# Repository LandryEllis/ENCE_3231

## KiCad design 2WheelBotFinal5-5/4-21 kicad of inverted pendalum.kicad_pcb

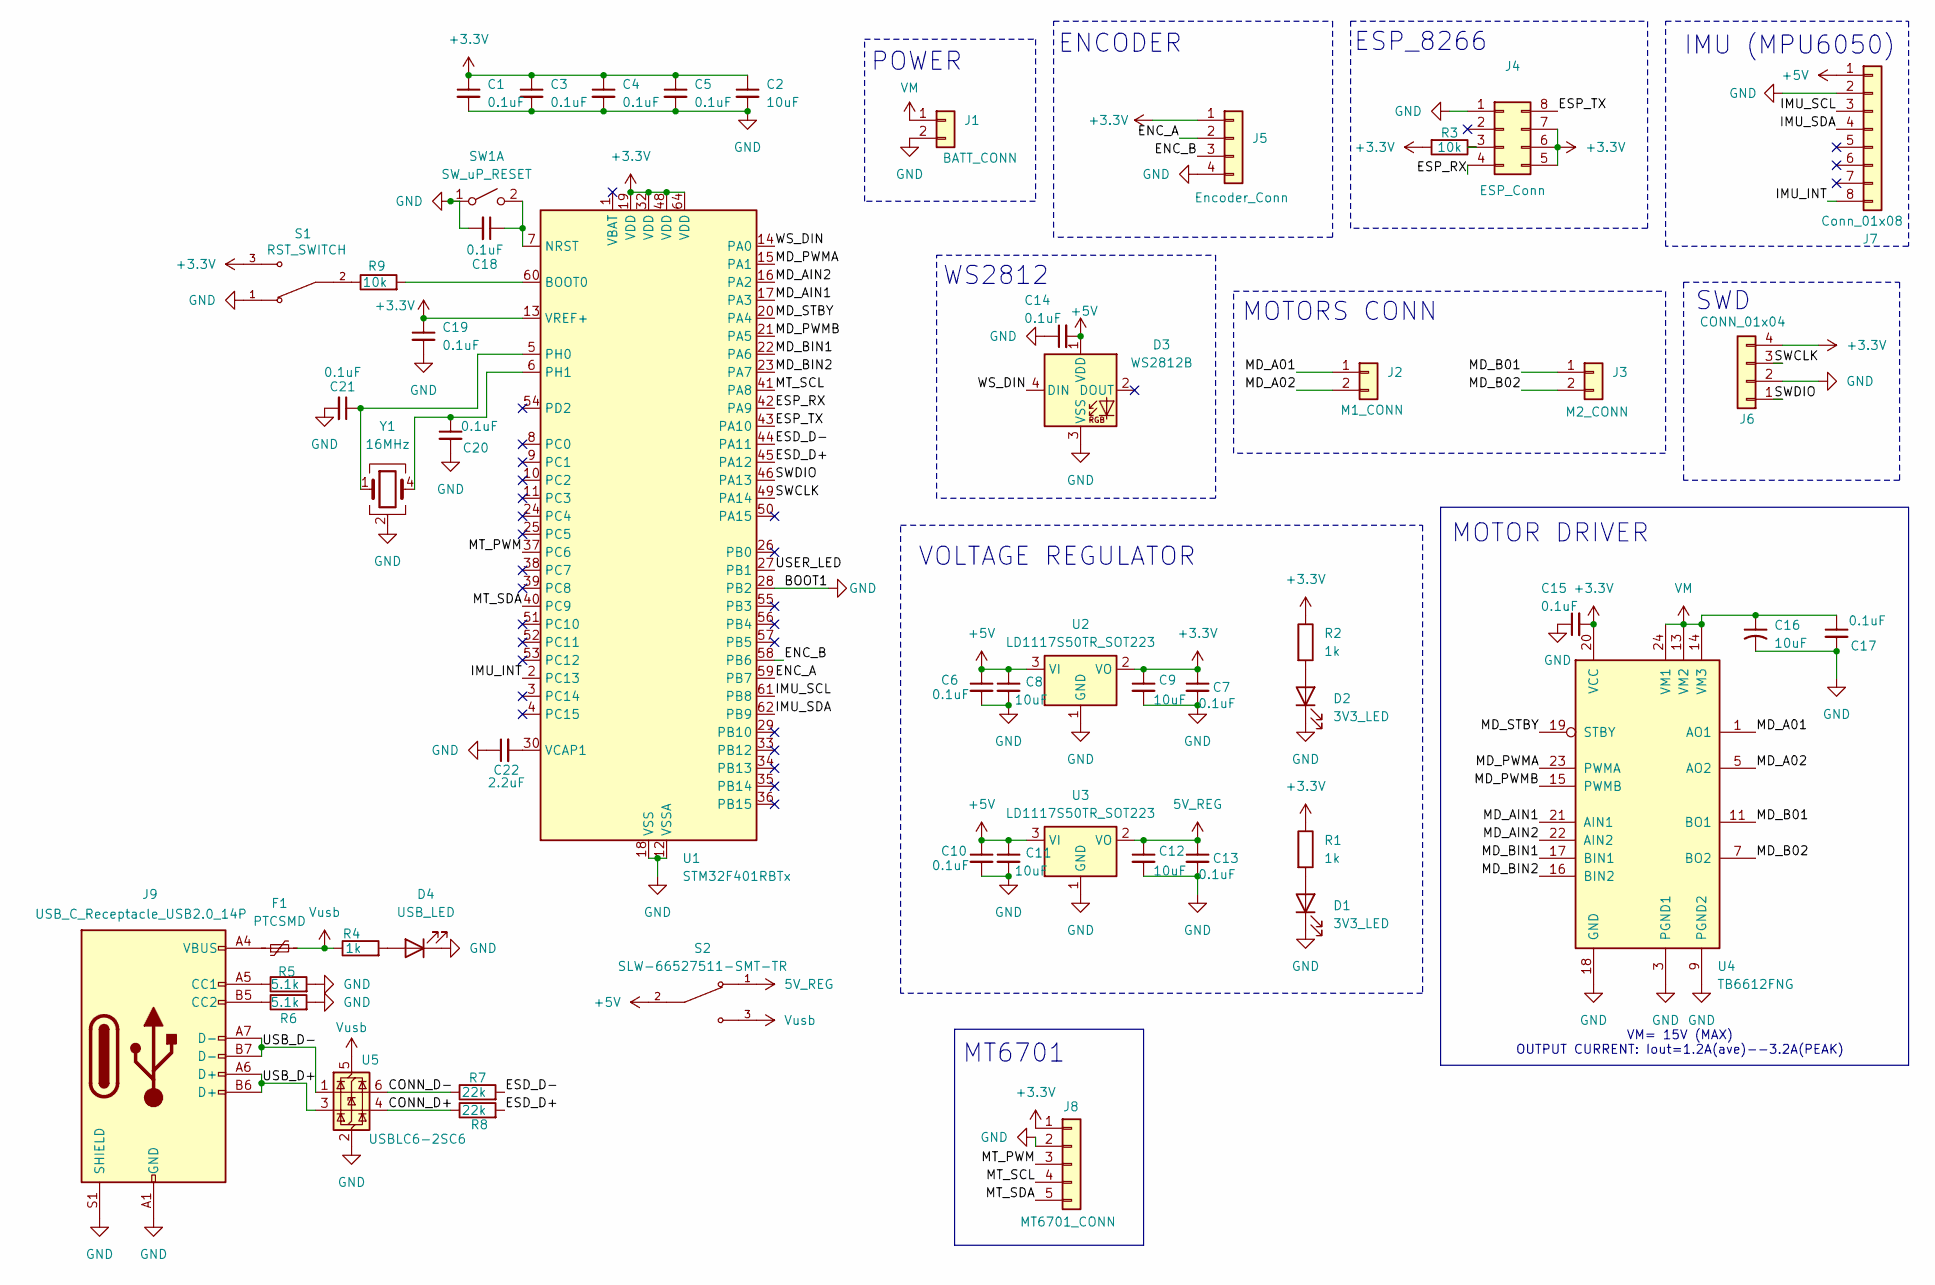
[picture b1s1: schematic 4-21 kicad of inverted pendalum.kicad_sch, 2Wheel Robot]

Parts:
C1, C3, C4, C5, C6, C7, C10, C13, C14, C15, C17, C18, C19, C20, C21: 0.1uF; C_0805_2012Metric_Pad1.18x1.45mm_HandSolder; mfr. # KYOCERA AVX
C2, C8, C9, C11, C12: 10uF; C_0805_2012Metric_Pad1.18x1.45mm_HandSolder; Mouser # 963-MCASL21GBB7106KT
C16: 10uF; C_0805_2012Metric_Pad1.18x1.45mm_HandSolder
C22: 2.2uF; C_0805_2012Metric_Pad1.18x1.45mm_HandSolder
D1, D2: 3V3_LED; LED_0805_2012Metric_Pad1.15x1.40mm_HandSolder
D3: WS2812B; LED_WS2812B_PLCC4_5.0x5.0mm_P3.2mm
D4: USB_LED; LED_0805_2012Metric_Pad1.15x1.40mm_HandSolder
F1: PTCSMD; Fuse_1812_4532Metric
J1: BATT_CONN; JST_XH_B2B-XH-A_1x02_P2.50mm_Vertical
J2: M1_CONN; JST_XH_B2B-XH-A_1x02_P2.50mm_Vertical
J3: M2_CONN; JST_XH_B2B-XH-A_1x02_P2.50mm_Vertical
J4: ESP_Conn; PinSocket_2x04_P2.54mm_Vertical
J5: Encoder_Conn; JST_XH_B4B-XH-A_1x04_P2.50mm_Vertical
J6: CONN_01x04; PinHeader_1x04_P2.54mm_Vertical
J7: Conn_01x08; PinSocket_1x08_P2.54mm_Vertical
J8: MT6701_CONN; JST_XH_B5B-XH-A_1x05_P2.50mm_Vertical
J9: USB_C_Receptacle_USB2.0_14P; USB_C_Receptacle_HCTL_HC-TYPE-C-16P-01A
R1, R2, R4: 1k; R_0805_2012Metric_Pad1.20x1.40mm_HandSolder
R3, R9: 10k; R_0805_2012Metric_Pad1.20x1.40mm_HandSolder
R5, R6: 5.1k; R_0805_2012Metric_Pad1.20x1.40mm_HandSolder
R7, R8: 22k; R_0805_2012Metric_Pad1.20x1.40mm_HandSolder
S1: RST_SWITCH; SW_SLW-66527511-SMT-TR; PARTREV 1.01
S2: SLW-66527511-SMT-TR; SW_SLW-66527511-SMT-TR; PARTREV 1.01
SW1: SW_uP_RESET; SW_uP_Reset
U1: STM32F401RBTx; LQFP-64_10x10mm_P0.5mm; Mfr. # STM32F401RET6
U2, U3: LD1117S50TR_SOT223; SOT-223-3_TabPin2; Mouser # 511-LD1117S50
U4: TB6612FNG; SSOP-24_5.3x8.2mm_P0.65mm
U5: USBLC6-2SC6; SOT-23-6
Y1: 16MHz; Crystal_SMD_Abracon_ABM8G-4Pin_3.2x2.5mm

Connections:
5V_REG: C12.1, C13.1, S2.1, U3.2 (VO)
+3.3V: C1.1, C2.1, C3.1, C4.1, C5.1, C7.1, C9.1, C15.2, C19.1, J4.5, J4.6, J4.7, J5.1, J6.4, J8.1, R1.1, R2.1, R3.2, S1.3, U1.13 (VREF+), U1.19 (VDD), U1.32 (VDD), U1.48 (VDD), U1.64 (VDD), U2.2 (VO), U4.20 (VCC)
+5V: C6.1, C8.1, C10.1, C11.1, C14.2, D3.1 (VDD), J7.1, S2.2, U2.3 (VI), U3.3 (VI)
/CONN_D+: R8.1, U5.4 (I/O2)
/CONN_D-: R7.1, U5.6 (I/O1)
/ENC_A: J5.2, U1.59 (PB7)
/ENC_B: J5.3, U1.58 (PB6)
/ESD_D+: R8.2, U1.45 (PA12)
/ESD_D-: R7.2, U1.44 (PA11)
/ESP_RX: J4.4, U1.42 (PA9)
/ESP_TX: J4.8, U1.43 (PA10)
/IMU_INT: J7.8, U1.2 (PC13)
/IMU_SCL: J7.3, U1.61 (PB8)
/IMU_SDA: J7.4, U1.62 (PB9)
/MD_A01: J2.1, U4.1 (AO1), U4.2 (AO1)
/MD_A02: J2.2, U4.5 (AO2), U4.6 (AO2)
/MD_AIN1: U1.17 (PA3), U4.21 (AIN1)
/MD_AIN2: U1.16 (PA2), U4.22 (AIN2)
/MD_B01: J3.1, U4.11 (BO1), U4.12 (BO1)
/MD_B02: J3.2, U4.7 (BO2), U4.8 (BO2)
/MD_BIN1: U1.22 (PA6), U4.17 (BIN1)
/MD_BIN2: U1.23 (PA7), U4.16 (BIN2)
/MD_PWMA: U1.15 (PA1), U4.23 (PWMA)
/MD_PWMB: U1.21 (PA5), U4.15 (PWMB)
/MD_STBY: U1.20 (PA4), U4.19 (STBY)
/MT_PWM: J8.3, U1.37 (PC6)
/MT_SCL: J8.4, U1.41 (PA8)
/MT_SDA: J8.5, U1.40 (PC9)
/SWCLK: J6.3, U1.49 (PA14)
/SWDIO: J6.1, U1.46 (PA13)
/USB_D+: J9.A6 (D+), J9.B6 (D+), U5.3 (I/O2)
/USB_D-: J9.A7 (D-), J9.B7 (D-), U5.1 (I/O1)
/USER_LED: U1.27 (PB1)
/WS_DIN: D3.4 (DIN), U1.14 (PA0)
GND: C1.2, C2.2, C3.2, C4.2, C5.2, C6.2, C7.2, C8.2, C9.2, C10.2, C11.2, C12.2, C13.2, C14.1, C15.1, C16.2, C17.2, C18.2, C19.2, C20.2, C21.2, C22.1, D1.1 (K), D2.1 (K), D3.3 (VSS), D4.1 (K), J1.2, J4.1, J5.4, J6.2, J7.2, J8.2, J9.A1 (GND), J9.A12 (GND), J9.B1 (GND), J9.B12 (GND), J9.S1 (SHIELD), R5.2, R6.2, S1.1, SW1.1 (A), U1.12 (VSSA), U1.18 (VSS), U1.28 (PB2), U1.31 (VSS), U1.47 (VSS), U1.63 (VSS), U2.1 (GND), U3.1 (GND), U4.3 (PGND1), U4.4 (PGND1), U4.9 (PGND2), U4.10 (PGND2), U4.18 (GND), U5.2 (GND), Y1.2 (G), Y1.3 (G)
unnamed: D1.2 (A), R1.2
unnamed: D2.2 (A), R2.2
unnamed: D4.2 (A), R4.2
unnamed: F1.1, J9.A4 (VBUS), J9.A9 (VBUS), J9.B4 (VBUS), J9.B9 (VBUS)
unnamed: J4.3, R3.1
unnamed: J9.A5 (CC1), R5.1
unnamed: J9.B5 (CC2), R6.1
unnamed: R9.1, S1.2
unnamed: C18.1, SW1.2 (B), U1.7 (NRST)
unnamed: R9.2, U1.60 (BOOT0)
unnamed: C21.1, U1.5 (PH0), Y1.1
unnamed: C20.1, U1.6 (PH1), Y1.4
unnamed: C22.2, U1.30 (VCAP1)
VM: C16.1, C17.1, J1.1, U4.13 (VM2), U4.14 (VM3), U4.24 (VM1)
Vusb: F1.2, R4.1, S2.3, U5.5 (VBUS)

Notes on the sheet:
VM= 15V (MAX) OUTPUT CURRENT: Iout=1.2A(ave)--3.2A(PEAK)
ESP_8266
IMU (MPU6050)
MT6701
SWD
MOTORS CONN
POWER
ENCODER
WS2812
VOLTAGE REGULATOR
MOTOR DRIVER

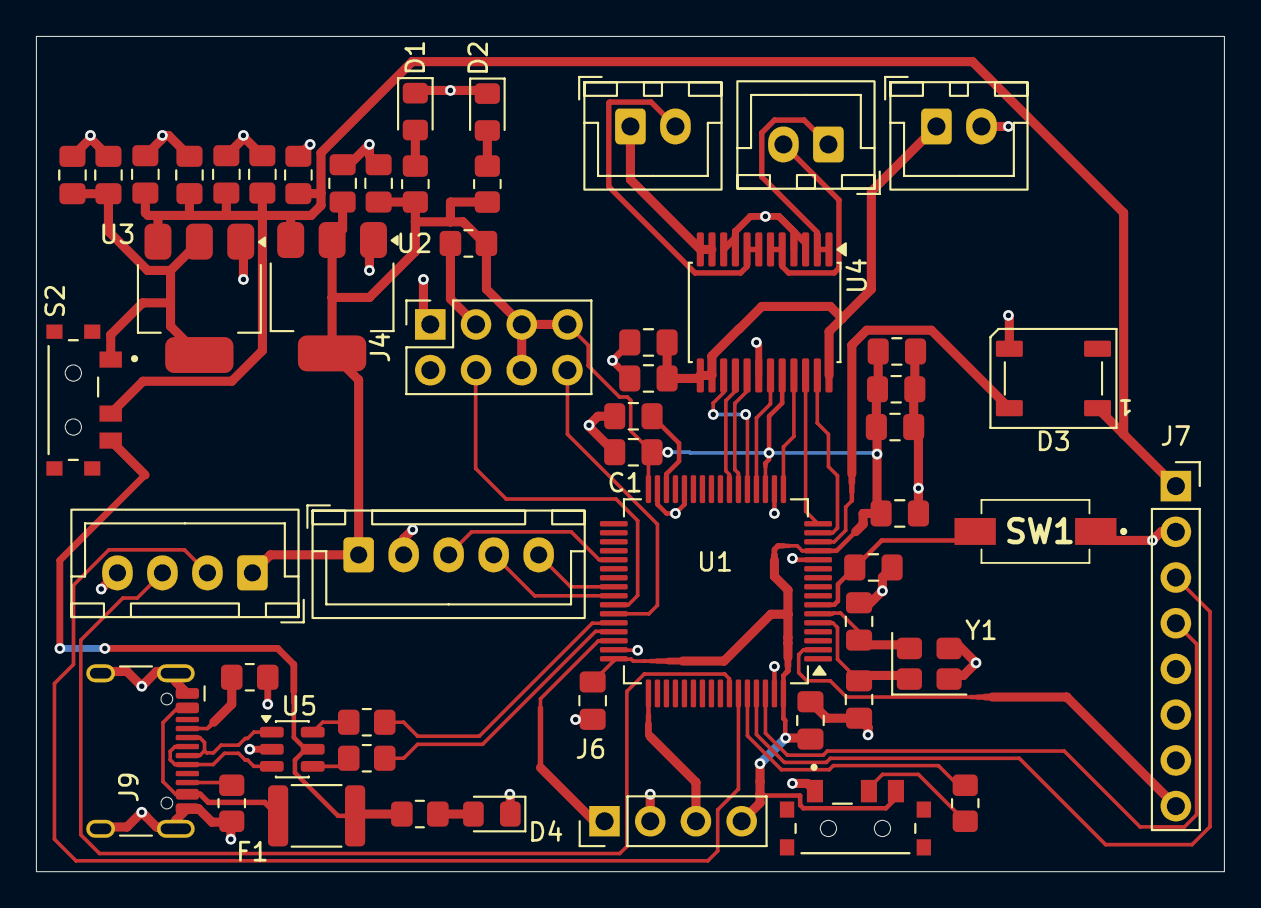
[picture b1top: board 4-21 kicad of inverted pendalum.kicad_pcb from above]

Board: 2 copper layers, 66.0 x 46.4 mm, 54 parts (0 on the bottom side), 49 nets.

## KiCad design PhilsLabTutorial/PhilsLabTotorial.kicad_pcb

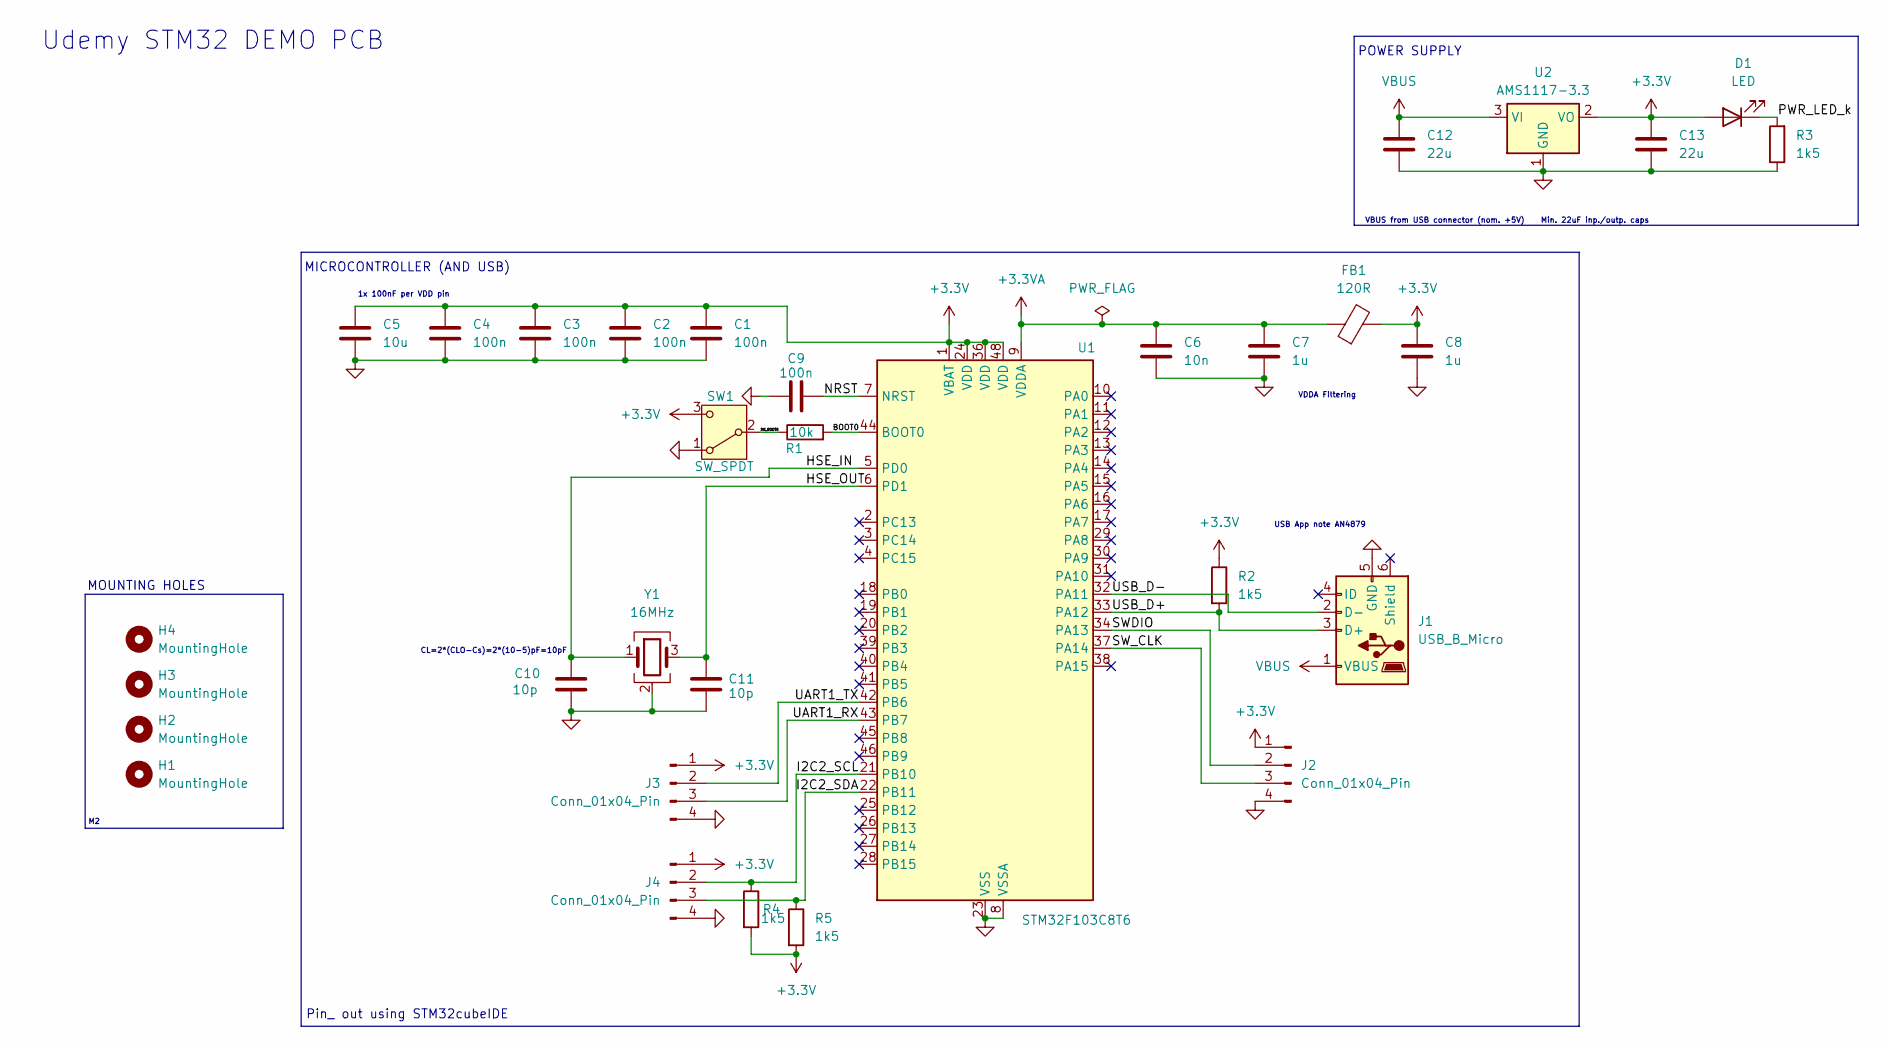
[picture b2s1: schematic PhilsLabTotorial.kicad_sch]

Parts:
C1, C2: 100n; C_0805_2012Metric
C3, C4, C9: 100n; C_0402_1005Metric
C5: 10u; C_0603_1608Metric
C6: 10n; C_0402_1005Metric
C7, C8: 1u; C_0402_1005Metric
C10, C11: 10p; C_0402_1005Metric
C12, C13: 22u; C_0402_1005Metric
D1: LED; LED_0603_1608Metric
FB1: 120R; L_0603_1608Metric
H1, H2, H3, H4: MountingHole; MountingHole_2.2mm_M2
J1: USB_B_Micro; USB_Micro-B_Wuerth_629105150521
J2, J3, J4: Conn_01x04_Pin; PinHeader_1x04_P2.54mm_Vertical
R1: 10k; R_0402_1005Metric
R2, R3, R4, R5: 1k5; R_0402_1005Metric
SW1: SW_SPDT; SW_SPDT_PCM12
U1: STM32F103C8T6; LQFP-48_7x7mm_P0.5mm
U2: AMS1117-3.3; SOT-223-3_TabPin2
Y1: 16MHz; Crystal_SMD_3225-4Pin_3.2x2.5mm

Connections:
+3.3V: C1.1, C2.1, C3.1, C4.1, C5.1, C8.1, C13.1, D1.2 (A), FB1.2, J2.1, J3.1, J4.1, R2.1, R4.2, R5.2, SW1.3 (C), U1.1 (VBAT), U1.24 (VDD), U1.36 (VDD), U1.48 (VDD), U2.2 (VO)
+3.3VA: C6.1, C7.1, FB1.1, U1.9 (VDDA)
/BOOT0: R1.2, U1.44 (BOOT0)
/HSE_IN: C10.1, U1.5 (PD0), Y1.1
/HSE_OUT: C11.1, U1.6 (PD1), Y1.3
/I2C2_SCL: J4.2, R4.1, U1.21 (PB10)
/I2C2_SDA: J4.3, R5.1, U1.22 (PB11)
/NRST: C9.2, U1.7 (NRST)
/PWR_LED_k: D1.1 (K), R3.2
/SWDIO: J2.2, U1.34 (PA13)
/SW_BOOT0: R1.1, SW1.2 (B)
/SW_CLK: J2.3, U1.37 (PA14)
/UART1_RX: J3.3, U1.43 (PB7)
/UART1_TX: J3.2, U1.42 (PB6)
/USB_D+: J1.3 (D+), R2.2, U1.33 (PA12)
/USB_D-: J1.2 (D-), U1.32 (PA11)
GND: C1.2, C2.2, C3.2, C4.2, C5.2, C6.2, C7.2, C8.2, C9.1, C10.2, C11.2, C12.2, C13.2, J1.5 (GND), J2.4, J3.4, J4.4, R3.1, SW1.1 (A), U1.8 (VSSA), U1.23 (VSS), U1.35 (VSS), U1.47 (VSS), U2.1 (GND), Y1.2 (G), Y1.4 (G)
VBUS: C12.1, J1.1 (VBUS), U2.3 (VI)

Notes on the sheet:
1x 100nF per VDD pin
MOUNTING HOLES
VDDA Filtering
CL=2*(CLO-Cs)=2*(10-5)pF=10pF
Pin_ out using STM32cubeIDE
MICROCONTROLLER (AND USB)
POWER SUPPLY
VBUS from USB connector (nom. +5V) Min. 22uF inp./outp. caps
USB App note AN4879
Udemy STM32 DEMO PCB

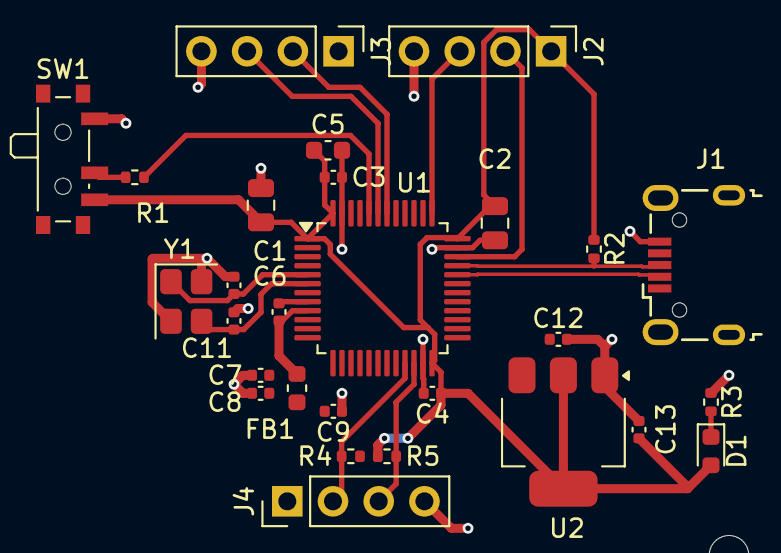
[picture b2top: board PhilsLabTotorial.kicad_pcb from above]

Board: 2 copper layers, 32 parts (0 on the bottom side), 18 nets.

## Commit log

2026-04-23 Add README.md file
2026-04-23 Rename README.md to 2WheelBotSchematic4-23/README.md
2026-04-28 Rename PhilsLabTutorial/PhilsLabTotorial.csv to PhilsLabTutorial/BOM/PhilsLabTotorial.csv
